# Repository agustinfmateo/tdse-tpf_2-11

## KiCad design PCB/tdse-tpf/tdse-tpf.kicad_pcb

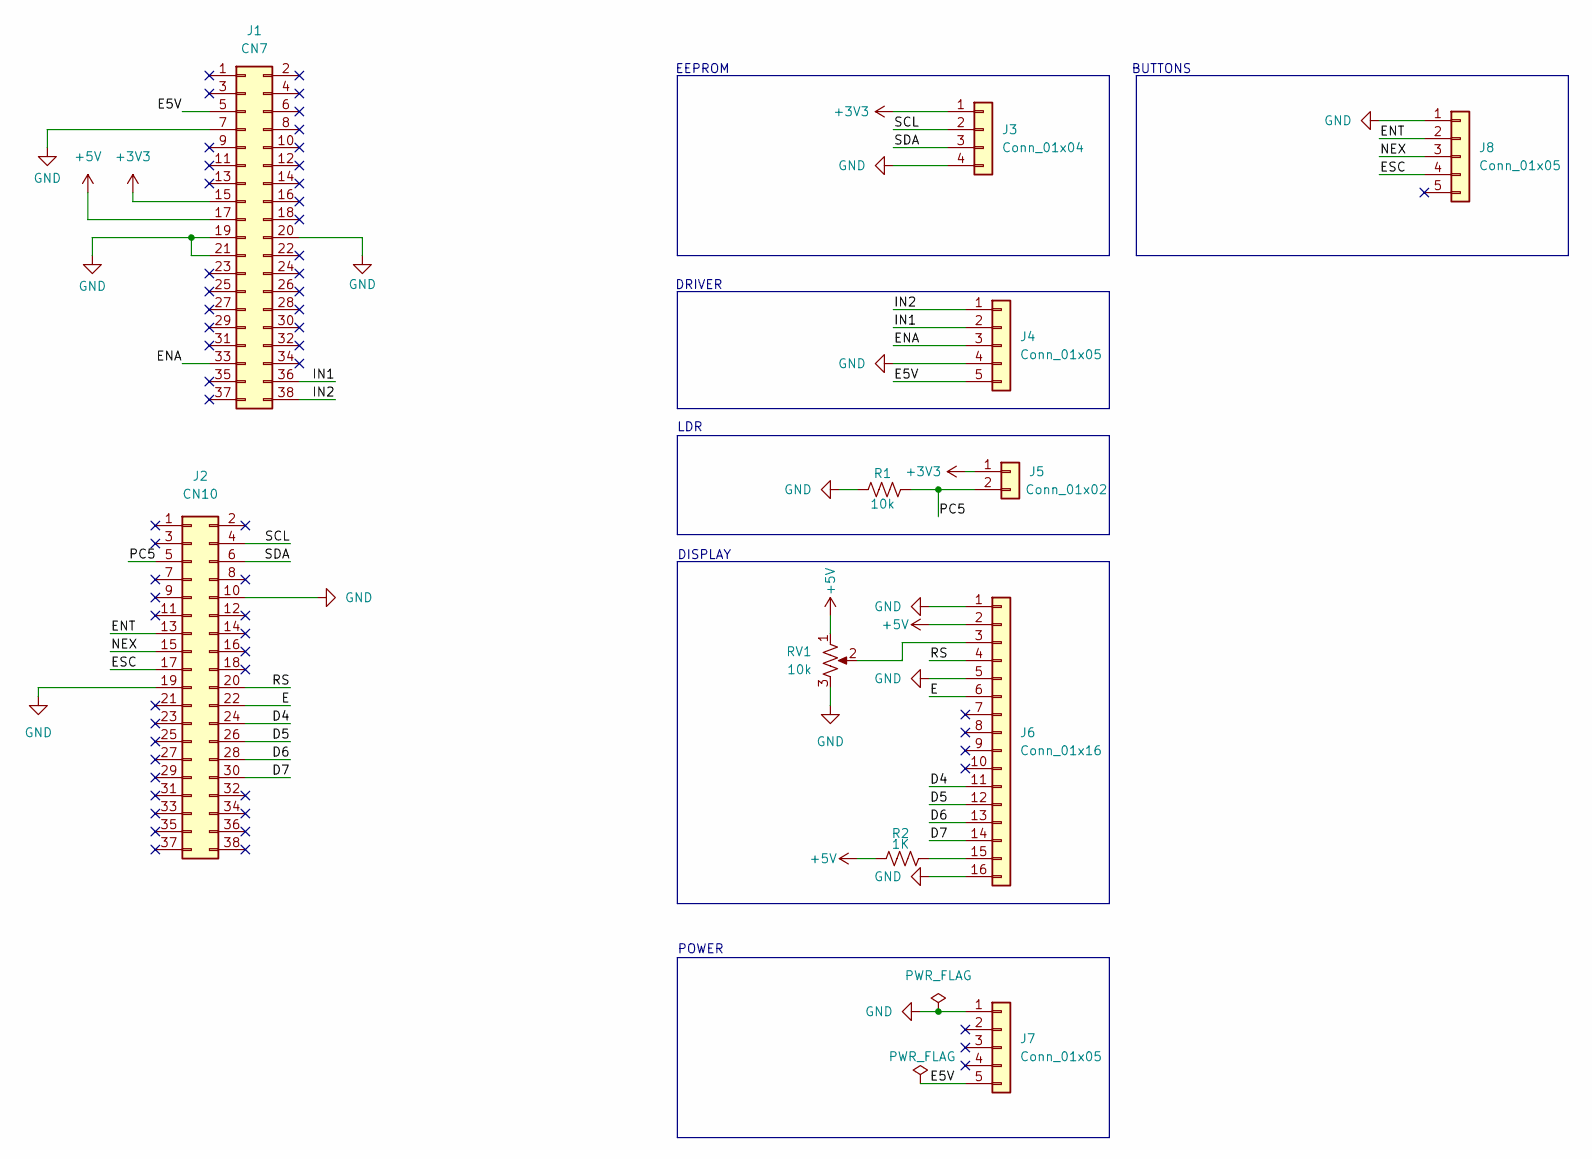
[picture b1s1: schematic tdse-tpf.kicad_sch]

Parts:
J1: CN7; PinSocket_2x19_P2.54mm_Vertical
J2: CN10; PinSocket_2x19_P2.54mm_Vertical
J3: Conn_01x04; PinSocket_1x04_P2.54mm_Vertical
J4, J8: Conn_01x05; PinHeader_1x05_P2.54mm_Vertical
J5: Conn_01x02; PinHeader_1x02_P2.54mm_Vertical
J6: Conn_01x16; PinSocket_1x16_P2.54mm_Vertical
J7: Conn_01x05; PinSocket_1x05_P2.54mm_Vertical
R1: 10k; R_Axial_DIN0204_L3.6mm_D1.6mm_P5.08mm_Horizontal
R2: 1K; R_Axial_DIN0204_L3.6mm_D1.6mm_P5.08mm_Horizontal
RV1: 10k; Potentiometer_ACP_CA6-H2,5_Horizontal

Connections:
+3V3: J1.15, J3.1, J5.1
+5V: J1.17, J6.2, R2.1, RV1.1
/D4: J2.24, J6.11
/D5: J2.26, J6.12
/D6: J2.28, J6.13
/D7: J2.30, J6.14
/E: J2.22, J6.6
/E5V: J1.5, J4.5, J7.5
/ENA: J1.33, J4.3
/ENT: J2.13, J8.2
/ESC: J2.17, J8.4
/IN1: J1.36, J4.2
/IN2: J1.38, J4.1
/NEX: J2.15, J8.3
/PC5: J2.5, J5.2, R1.2
/RS: J2.20, J6.4
/SCL: J2.4, J3.2
/SDA: J2.6, J3.3
GND: J1.7, J1.19, J1.20, J1.21, J2.10, J2.19, J3.4, J4.4, J6.1, J6.5, J6.16, J7.1, J8.1, R1.1, RV1.3
unnamed: J6.3, RV1.2
unnamed: J6.15, R2.2

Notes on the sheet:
LDR
DISPLAY
BUTTONS
EEPROM
DRIVER
POWER

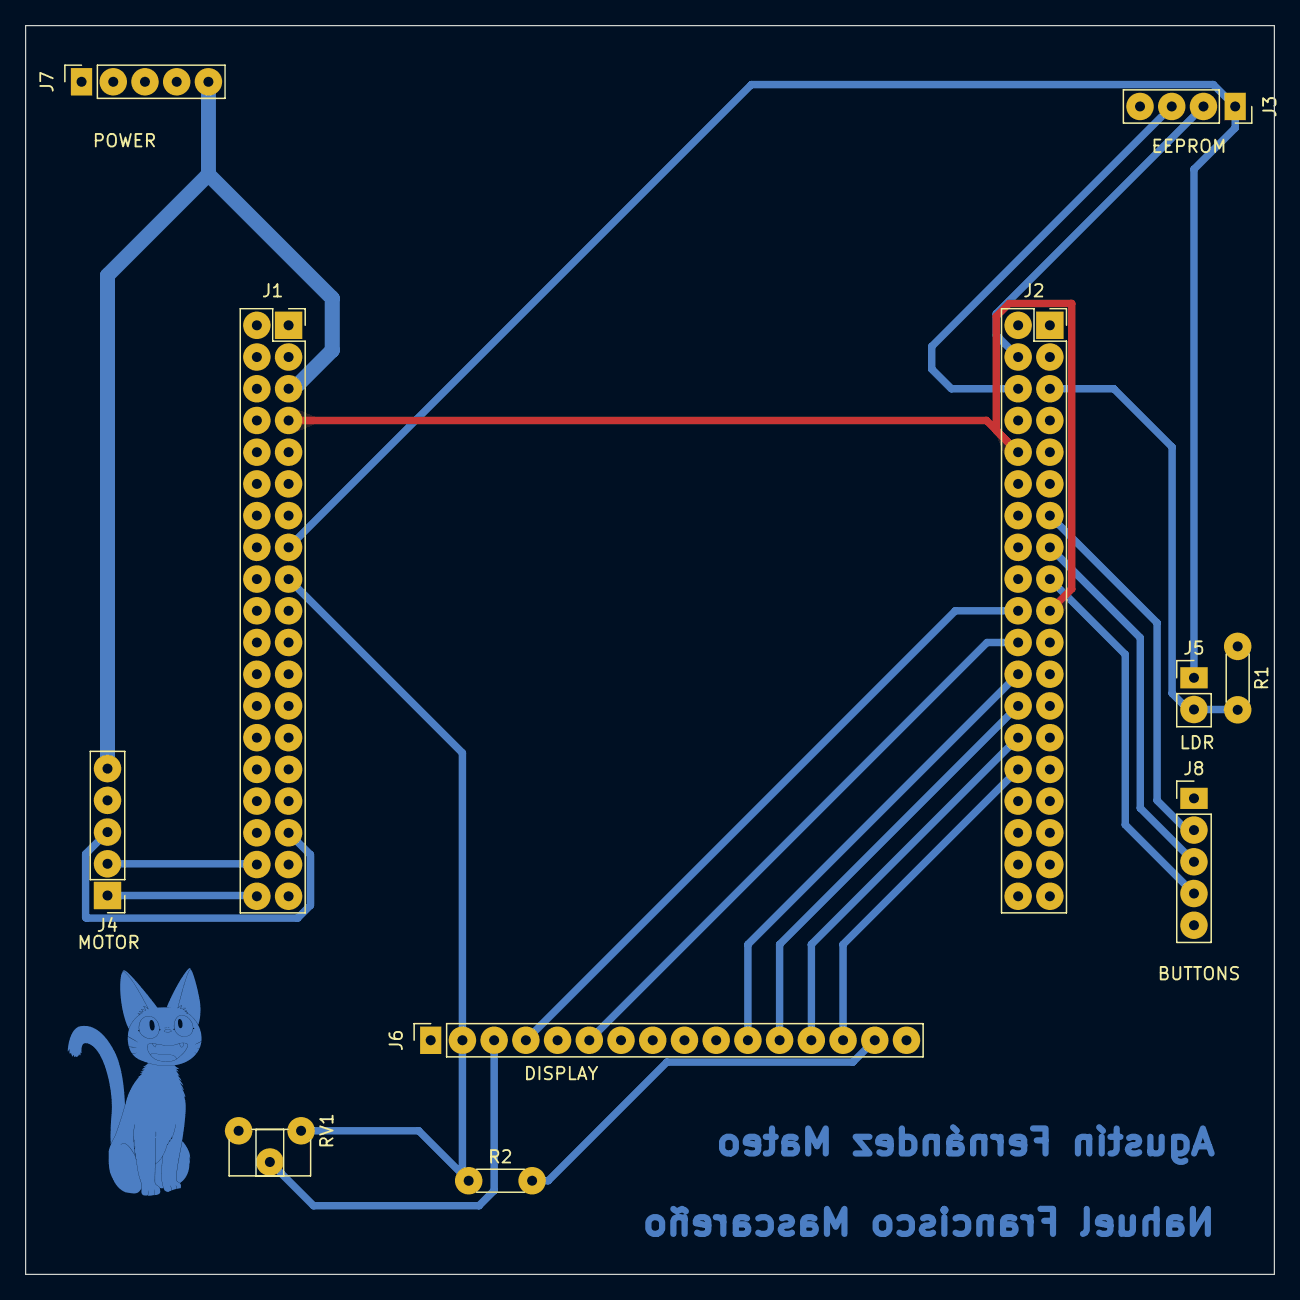
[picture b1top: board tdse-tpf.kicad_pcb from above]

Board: 2 copper layers, 100.0 x 100.0 mm, 11 parts (0 on the bottom side), 21 nets.

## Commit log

2026-01-25 update state-transition table
2026-02-06 added actuator states - changed motor.c to non blocking
2026-02-06 Fix HALIrqHandler - Fix states
2026-02-07 test integration
2026-02-08 Ignore IDE metadata and removed from repo
2026-02-08 Added logger config
2026-02-13 Added eeprom read/write functions and eeprom states
2026-02-15 minor fixes eeprom_check_and_load & find_latest_slot
2026-02-15 added all last changes clock-display-actuator-sleep
2026-02-16 Added PCB layout
2026-02-18 Changed pins sensor-ldr-display & updated pcb pads
2026-02-18 Change LDR ADC to non-continuous mode
2026-02-20 Updated functions used in task_menu & moved cfg structs
2026-02-20 Changed task_actuator now uses global config struct & moveMotor now only uses cfg structure
2026-02-20 Moved cfg structs to system_cfg_attribute.h and minor fixes
2026-02-21 Changed task_ldr & task_clock now use the global cfg structure & minor fixes
2026-02-24 update sleep mode, add open/close functions to task_menu
2026-02-24 update of the blind opening configuration
2026-02-25 minor fixes
2026-02-27 Fixed GPIO Pull ups
2026-02-28 Changed task_ldr now check mode & counter bug fixed
2026-02-28 Fixed bug in Disable & Enable IRQ btn_a in task_menu
2026-02-28 minor fix
2026-03-01 Eliminated LDR logic in task_clock
2026-03-01 Added pull_ups in .ioc
2026-03-01 update task_menu.c - add new state and event
2026-03-01 Duplicated code removed from task_menu
2026-03-01 Added tasks tick definition
2026-03-01 Made display non blocking
2026-03-02 Fixed init bug
2026-03-02 Fixed next state memory reset & minor fixes
2026-03-02 Fixed wcet sleep bug & minor fixes
2026-03-02 Fix ldr measuring time
2026-03-02 Fixed bug sleep after measuring ldr & bug fix in menu
2026-03-02 Fixed bug in the opening configuration
2026-03-02 Fixed bug ST_SET_UP_MENU_ERASE_MEMORY
2026-03-03 Fixed bug check opening
2026-03-03 Deleted all LOGGER functions
